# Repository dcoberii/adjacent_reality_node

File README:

Copy 99-dfu_programmer.rules to /etc/udev/rules.d to use with non-root users

Status:
  avr_src/fusion_raw.c 			incomplete and untested (hardware unavailable)
  avr_src/twi.*				complete, may add features later
  avr_src/l3g4200d.* lsm3003dlm.*	simple but complete, may add features later
  avr_src/usb_hid.*			grotty but barely functional, will be replaced (priority)
  avr_src/Makefile			got a little overzealous with the dependencies

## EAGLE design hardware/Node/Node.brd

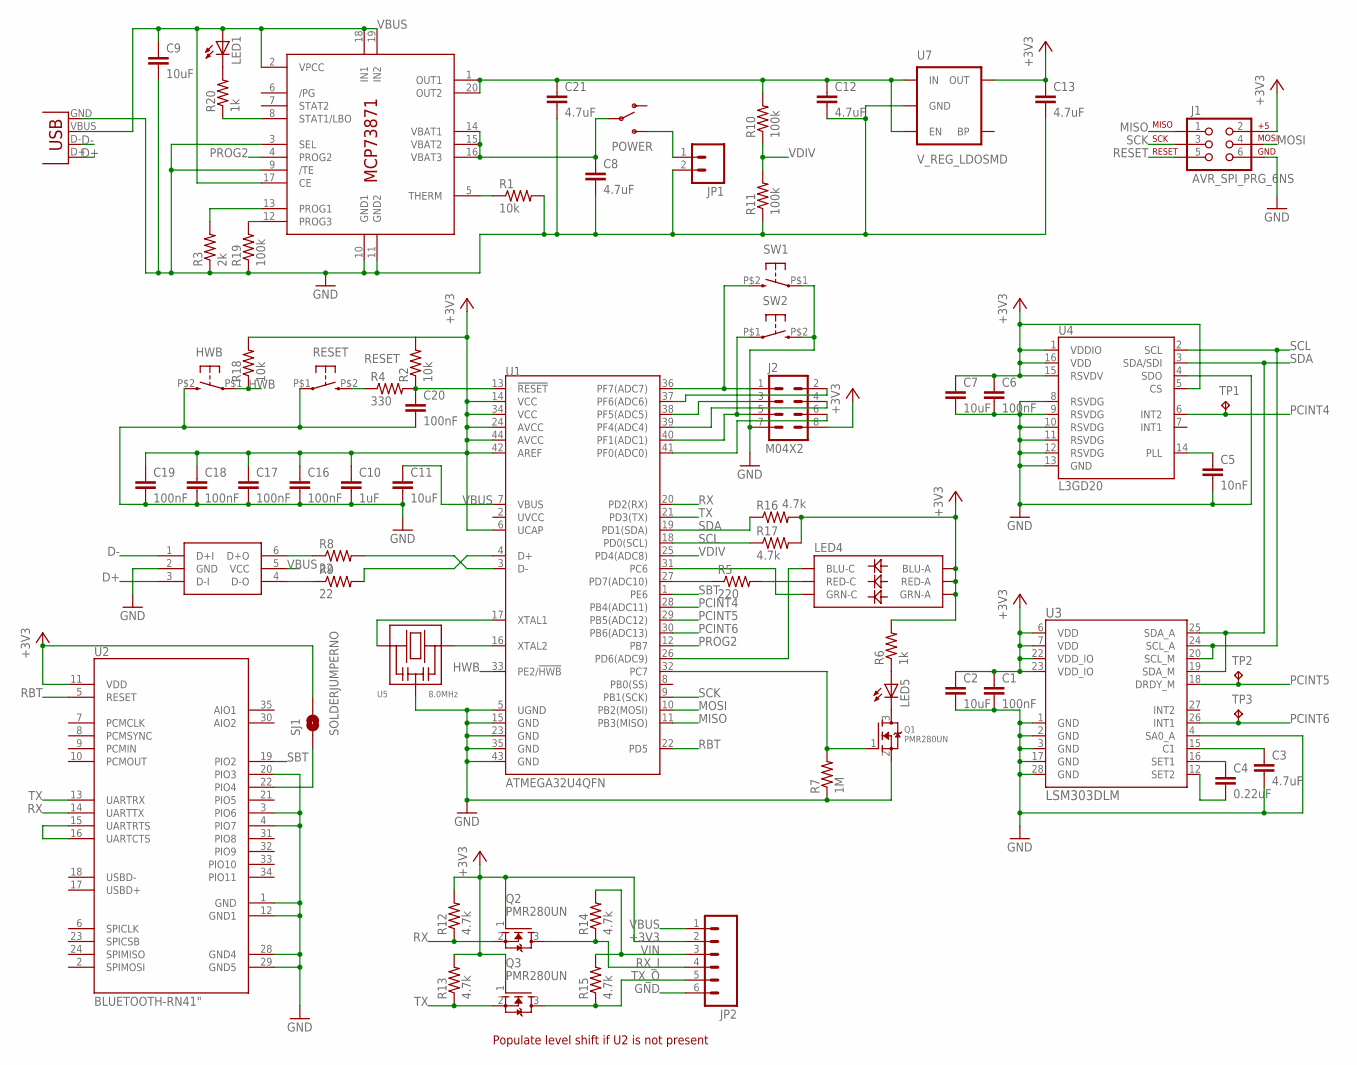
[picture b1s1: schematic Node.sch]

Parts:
C1, C6, C16, C17, C18, C19, C20: 100nF; 0402-CAP
C2, C7, C9, C11: 10uF; 0603-CAP
C3, C8, C12, C13, C21: 4.7uF; 0603-CAP
C4: 0.22uF; 0402-CAP
C5: 10nF; 0402-CAP
C10: 1uF; 0402-CAP
HWB: KSS
J1: AVR_SPI_PRG_6NS; 2X3-NS
J2: M04X2; 2X4
JP1: M02-JST-2MM-SMT; JST-2-SMD
JP2: M06SIP; 1X06
LED1, LED5: LED0603; LED-0603
LED4: LED-TRICOLOR-5050LED-TRICOLOR-0606; 0606
POWER: SWITCH-SPST-SMD-A
Q1, Q2, Q3: PMR280UN; SOT416
R1, R2, R18: 10k; 0402-RES
R3: 2k; 0402-RES
R4: 330; 0402-RES
R5: 220; 0402-RES
R6, R20: 1k; 0402-RES
R7: 1M; 0402-RES
R8, R9: 22; 0402-RES
R10, R11, R19: 100k; 0402-RES
R12, R13, R14, R15, R16, R17: 4.7k; 0402-RES
RESET: KSS
SJ1: SOLDERJUMPERNO; SJ_2S-NO
SW1, SW2: KSS
TP1, TP2, TP3: TPTP06R; TP06R
U1: ATMEGA32U4QFN; QFN-44
U2: BLUETOOTH-RN41"; RN41
U3: LSM303DLM; LGA28-5X5
U4: L3GD20; LGA16-4X4
U5: 8.0MHz; SMT_RESONATOR_3731
U6: MCP73871; QFN20
U7: V_REG_LDOSMD; SOT23-5
U9: RCLAMP0502A; SOT-666
X1: USBSMD; USB-MINIB

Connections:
+3V3: C1.1, C2.1, C6.1, C7.1, C10.1, C13.1, C16.1, C17.1, C18.1, C19.1, J1.2, J2.8, JP2.2, LED4.4 (BLU-A), LED4.5 (RED-A), LED4.6 (GRN-A), Q2.1 (G), Q3.1 (G), R2.2, R6.2, R12.2, R13.2, R16.2, R17.2, R18.2, SJ1.2, U1.6 (UCAP), U1.14 (VCC), U1.24 (AVCC), U1.34 (VCC), U1.42 (AREF), U1.44 (AVCC), U2.11 (VDD), U3.6 (VDD), U3.7 (VDD), U3.22 (VDD_IO), U3.23 (VDD_IO), U4.1 (VDDIO), U4.5 (CS), U4.15 (RSVDV), U4.16 (VDD), U7.5 (OUT)
D+: U9.3 (D-I), X1.D+
D-: U9.1 (D+I), X1.D-
GND: C1.2, C2.2, C3.2, C5.2, C6.2, C7.2, C8.2, C9.2, C10.2, C11.2, C12.2, C13.2, C16.2, C17.2, C18.2, C19.2, C20.2, C21.2, HWB.P$2 (3), J1.6, J2.7, JP1.2, JP2.6, Q1.2 (S), R1.2, R3.1, R7.1, R11.1, R19.1, RESET.P$1 (1), SW1.P$1 (1), SW2.P$2 (3), U1.5 (UGND), U1.15 (GND), U1.23 (GND), U1.35 (GND), U1.43 (GND), U2.1 (GND), U2.3 (PIO6), U2.4 (PIO7), U2.12 (GND1), U2.20 (PIO3), U2.28 (GND4), U2.29 (GND5), U3.1 (GND), U3.2 (GND), U3.3 (GND), U3.4 (SA0_A), U3.17 (GND), U3.28 (GND), U4.4 (SDO), U4.8 (RSVDG), U4.9 (RSVDG), U4.10 (RSVDG), U4.11 (RSVDG), U4.12 (RSVDG), U4.13 (GND), U5.P$2 (GND), U6.3 (SEL), U6.9 (/TE), U6.10 (GND1), U6.11 (GND2), U7.2 (GND), U9.2 (GND), X1.GND
HWB: HWB.P$1 (1), R18.1, U1.33 (PE2/!HWB)
MISO: J1.1, U1.11 (PB3(MISO))
MOSI: J1.4, U1.10 (PB2(MOSI))
unnamed: U1.16 (XTAL2), U5.P$3 (2)
unnamed: U1.17 (XTAL1), U5.P$1 (1)
unnamed: C3.1, U3.15 (C1)
unnamed: C8.1, POWER.2, U6.14 (VBAT1), U6.15 (VBAT2), U6.16 (VBAT3)
unnamed: C4.1, U3.16 (SET1)
unnamed: C4.2, U3.12 (SET2)
unnamed: C5.1, U4.14 (PLL)
unnamed: R1.1, U6.5 (THERM)
unnamed: U2.15 (UARTRTS), U2.16 (UARTCTS)
unnamed: LED4.2 (RED-C), R5.2
unnamed: C12.1, C21.1, R10.2, U6.1 (OUT1), U6.20 (OUT2), U7.1 (IN), U7.3 (EN)
unnamed: LED4.3 (GRN-C), U1.31 (PC6)
unnamed: LED1.C, R20.2
unnamed: SJ1.1, U2.22 (PIO4)
unnamed: R8.2, U1.3 (D-)
unnamed: R3.2, U6.13 (PROG1)
unnamed: LED4.1 (BLU-C), U1.26 (PD6(ADC9))
unnamed: R5.1, U1.27 (PD7(ADC10))
unnamed: R20.1, U6.8 (STAT1/LBO)
unnamed: LED5.C, Q1.3 (D)
unnamed: LED5.A, R6.1
unnamed: Q1.1 (G), R7.2, U1.32 (PC7)
unnamed: R9.2, U1.4 (D+)
unnamed: R8.1, U9.6 (D+O)
unnamed: R9.1, U9.4 (D-O)
unnamed: C20.1, R2.1, R4.2, U1.13 (!RESET)
unnamed: J2.1, SW1.P$2 (3), U1.36 (PF7(ADC7))
unnamed: JP1.1, POWER.3 (S)
unnamed: J2.2, U1.37 (PF6(ADC6))
unnamed: J2.3, U1.38 (PF5(ADC5))
unnamed: J2.4, U1.39 (PF4(ADC4))
unnamed: J2.5, SW2.P$1 (1), U1.40 (PF1(ADC1))
unnamed: J2.6, U1.41 (PF0(ADC0))
unnamed: R19.2, U6.12 (PROG3)
PCINT4: TP1.TP, U1.28 (PB4(ADC11)), U4.6 (INT2)
PCINT5: TP2.TP, U1.29 (PB5(ADC12)), U3.18 (DRDY_M)
PCINT6: TP3.TP, U1.30 (PB6(ADC13)), U3.26 (INT1)
PROG2: U1.12 (PB7), U6.4 (PROG2)
RBT: U1.22 (PD5), U2.5 (RESET)
RESET: J1.5, R4.1, RESET.P$2 (3)
RX: Q2.2 (S), R12.1, U1.20 (PD2(RX)), U2.14 (UARTTX)
RX_I: JP2.4, Q2.3 (D), R14.1
SBT: U1.1 (PE6), U2.19 (PIO2)
SCK: J1.3, U1.9 (PB1(SCK))
SCL: R17.1, U1.18 (PD0(SCL)), U3.20 (SCL_M), U3.24 (SCL_A), U4.2 (SCL)
SDA: R16.1, U1.19 (PD1(SDA)), U3.19 (SDA_M), U3.25 (SDA_A), U4.3 (SDA/SDI)
TX: Q3.2 (S), R13.1, U1.21 (PD3(TX)), U2.13 (UARTRX)
TX_O: JP2.5, Q3.3 (D), R15.1
VBUS: C9.1, C11.1, JP2.1, LED1.A, U1.7 (VBUS), U6.2 (VPCC), U6.17 (CE), U6.18 (IN1), U6.19 (IN2), U9.5 (VCC), X1.VBUS
VDIV: R10.1, R11.2, U1.25 (PD4(ADC8))
VIN: JP2.3, R14.2, R15.2

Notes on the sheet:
Populate level shift if U2 is not present

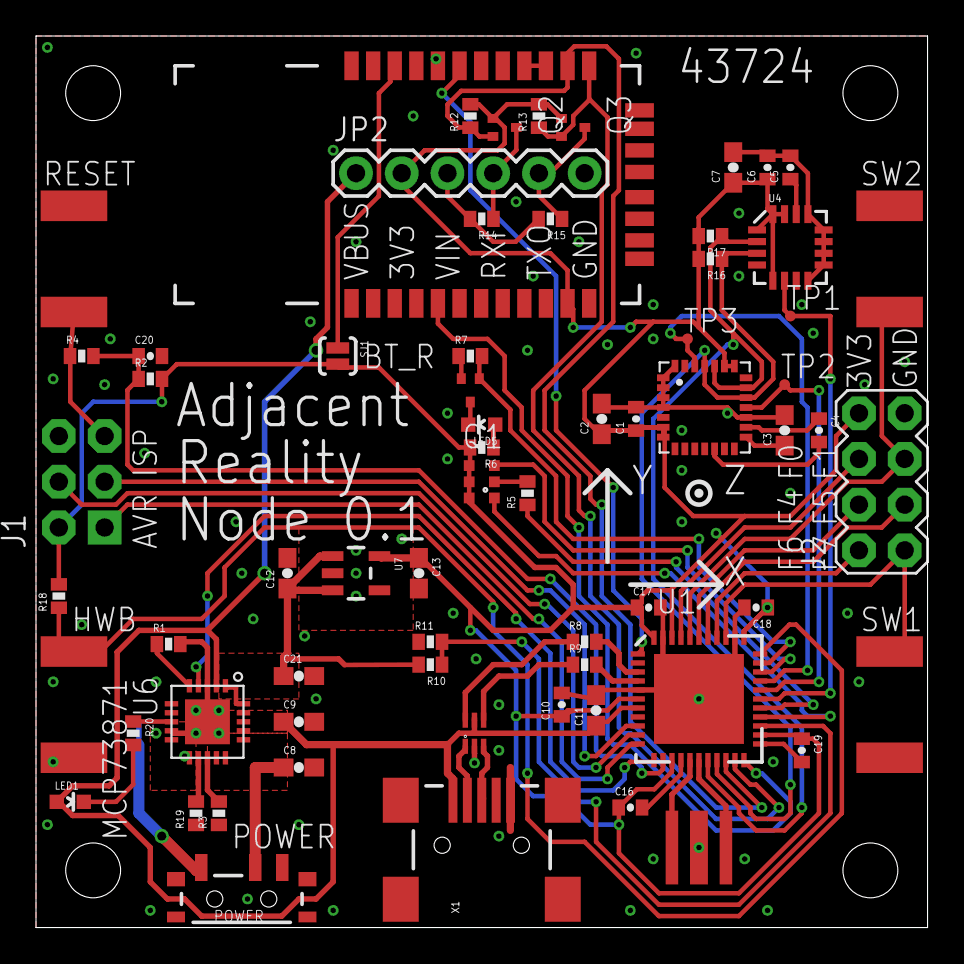
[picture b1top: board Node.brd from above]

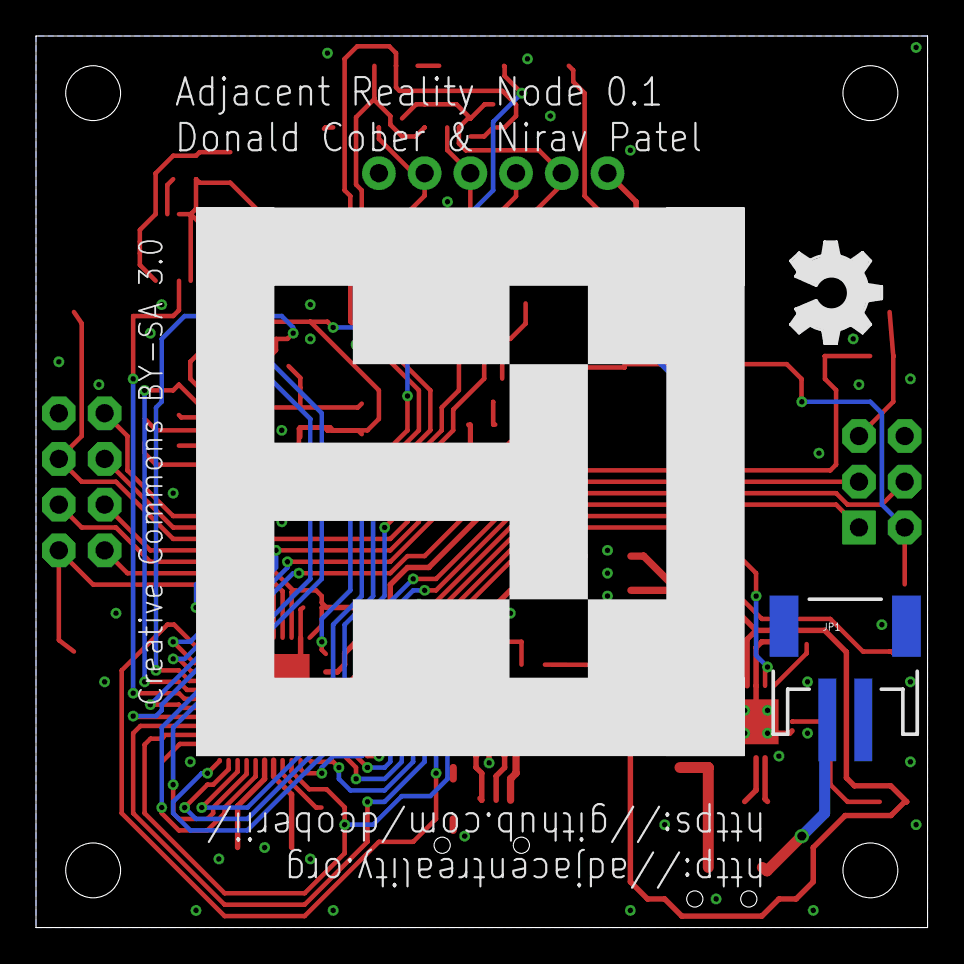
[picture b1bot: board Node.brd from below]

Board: 2 copper layers, 49.5 x 49.5 mm, 72 parts (2 on the bottom side), 58 nets.

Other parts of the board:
OSHW: OSHW_FILLX200_NOTEXT
U$1, U$2, U$3, U$4: STAND-OFF-TIGHT

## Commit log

2011-12-05 Adds the basic code to stream raw sensor values across some hid messages Not complete or functional
2011-12-08 Added header for hid sensors (from usb hid docu) no change in function
2011-12-29 a start on a schemetic for the Node
2011-12-30 Changed from usb hid to usb cdc acm By disabling the line coding options and handling the RX in an endpoint interrupt, these things actually look fairly similar
    Firmware is functional enough to collect raw data for offline fusion testing
2012-01-10 Complete alpha revision schematic
2012-01-10 Added nfet style level shift Moved switch to other side of MAX1704x Changed C1 value from 100uF to 100nF Changed U1 symbol from NPN to NFET Added optional pullups on SDA/SCL Pullup on HWB Changed res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
2012-01-21 use mcp73871 and cleanup
2012-01-22 start of board layout
2012-01-22 switched mosfets
2012-01-22 put vbus on the header
2012-01-26 Start of laying out traces
2012-01-27 Routing more of the easy traces
2012-01-28 route more of the breakouts
2012-01-29 reorder some pins
2012-01-29 route low battery led
2012-01-30 move stuff to meet the DRC
2012-01-30 fix packages, route ISP
2012-01-31 route LEDs and interrupts
2012-01-31 lay ground pours
2012-01-31 moved a trace to make the bottom fully connected
2012-02-01 expand keepout to board edge, fix ground pours
2012-02-01 added vias, 1 airwire left!!!
2012-02-01 Ratsnest: Nothing to do!
2012-02-02 Add labels
2012-02-03 make the fiducial aruco compatible
2012-02-03 add Seeed order number to silkscreen
2012-02-13 split the hardware into a new repo at https://github.com/AdjacentReality/NodeHardware
2012-02-26 Fixed used config descript, added self test
2012-02-26 Fixed makefile for generic target.hex make selftest.hex now works

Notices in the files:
hardware/Node/Node.brd:
Creative Commons BY-SA 3.0
parts and their libraries:
SparkFun: Licensing: CC v3.0 Share-Alike You are welcome to use this library for commercial purposes.
